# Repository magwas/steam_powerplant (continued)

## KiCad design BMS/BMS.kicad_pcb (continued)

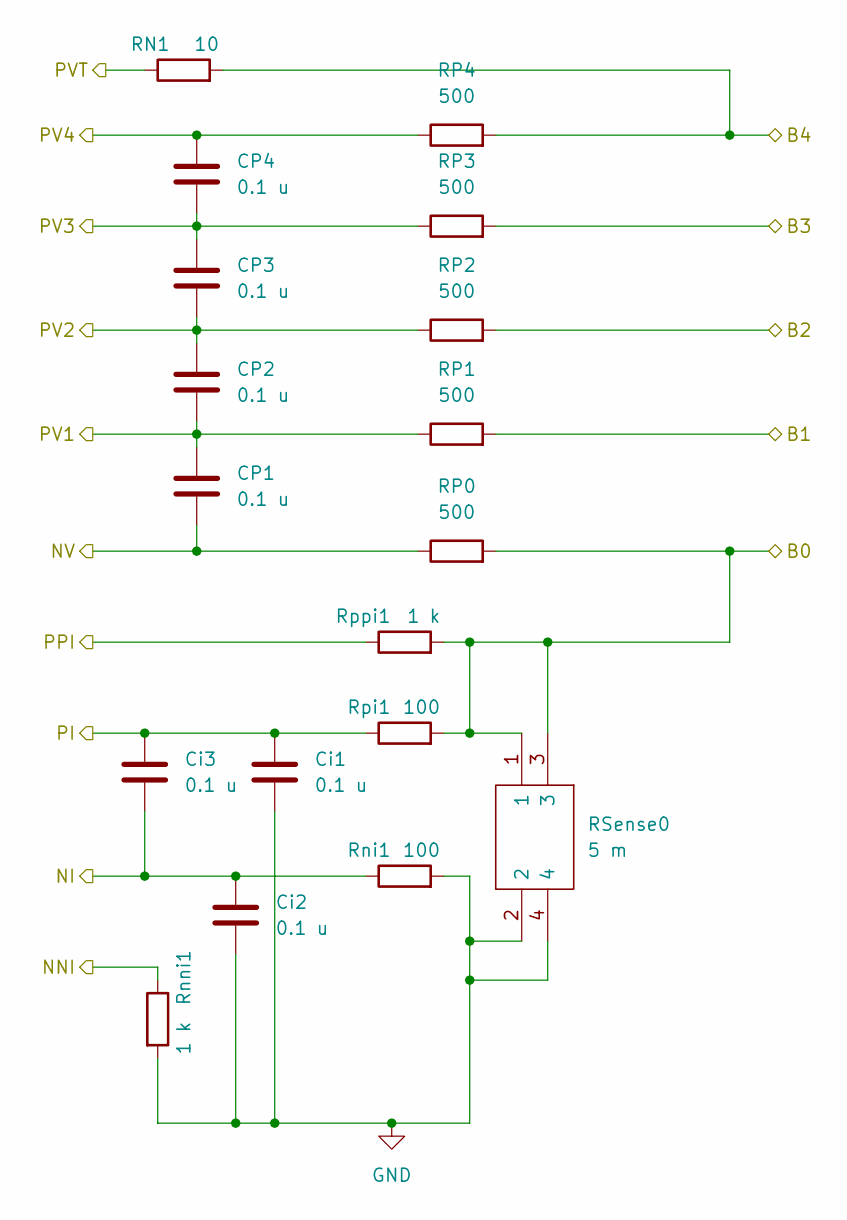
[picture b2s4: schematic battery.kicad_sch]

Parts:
CP1, CP2, CP3, CP4: 0.1 u; C_0603_1608Metric; Manufacturer_Part_Number KAM15AR71H104KT
Ci1, Ci2, Ci3: 0.1 u; C_0603_1608Metric; Manufacturer_Part_Number KAM15AR71H104KT
RN1: 10; R_0402_1005Metric; Manufacturer_Part_Number ERJ-U0XF10R0Y
RP0, RP1, RP2, RP3, RP4: 500; R_1206_3216Metric; Manufacturer_Part_Number MCA12060D5000BP500
RSense0: 5 m; Y14880R00500B9R; Mouser Part Number 71-CSM36370R0050BST
Rni1: 100; R_0603_1608Metric; Manufacturer_Part_Number APC0603T100RZ
Rnni1: 1 k; R_0402_1005Metric; Manufacturer_Part_Number 71-PTN0402Y5000BST1
Rpi1: 100; R_0603_1608Metric; Manufacturer_Part_Number APC0603T100RZ
Rppi1: 1 k; R_0402_1005Metric; Manufacturer_Part_Number 71-PTN0402Y5000BST1

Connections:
/Battery/B0: RP0.2, RSense0.1, RSense0.3, Rpi1.2, Rppi1.2; also elsewhere on the board
/Battery/B1: RP1.2; also elsewhere on the board
/Battery/B2: RP2.2; also elsewhere on the board
/Battery/B3: RP3.2; also elsewhere on the board
/Battery/B4: RN1.2, RP4.2; also elsewhere on the board
/Battery/NI: Ci2.2, Ci3.1, Rni1.1; also elsewhere on the board
/Battery/NNI: Rnni1.1; also elsewhere on the board
/Battery/NV: CP1.1, RP0.1; also elsewhere on the board
/Battery/PI: Ci1.2, Ci3.2, Rpi1.1; also elsewhere on the board
/Battery/PPI: Rppi1.1; also elsewhere on the board
/Battery/PV1: CP1.2, CP2.1, RP1.1; also elsewhere on the board
/Battery/PV2: CP2.2, CP3.1, RP2.1; also elsewhere on the board
/Battery/PV3: CP3.2, CP4.1, RP3.1; also elsewhere on the board
/Battery/PV4: CP4.2, RP4.1; also elsewhere on the board
/Battery/PVT: RN1.1; also elsewhere on the board
GND: Ci1.1, Ci2.1, RSense0.2, RSense0.4, Rni1.2, Rnni1.2; also elsewhere on the board

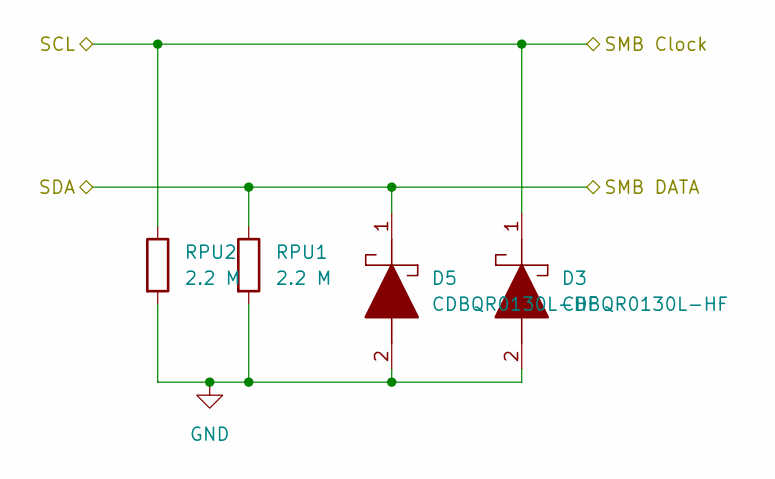
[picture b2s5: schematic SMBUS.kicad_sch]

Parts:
D3, D5: CDBQR0130L-HF; D_0402_1005Metric; Manufacturer_Part_Number CDBQR0130L-HF
RPU1, RPU2: 2.2 M; R_2010_5025Metric; Manufacturer_Part_Number RCV20102M20JNEF

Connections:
/SMBUS/SCL: D3.1, RPU2.1; also elsewhere on the board
/SMBUS/SDA: D5.1, RPU1.1; also elsewhere on the board
GND: D3.2, D5.2, RPU1.2, RPU2.2; also elsewhere on the board

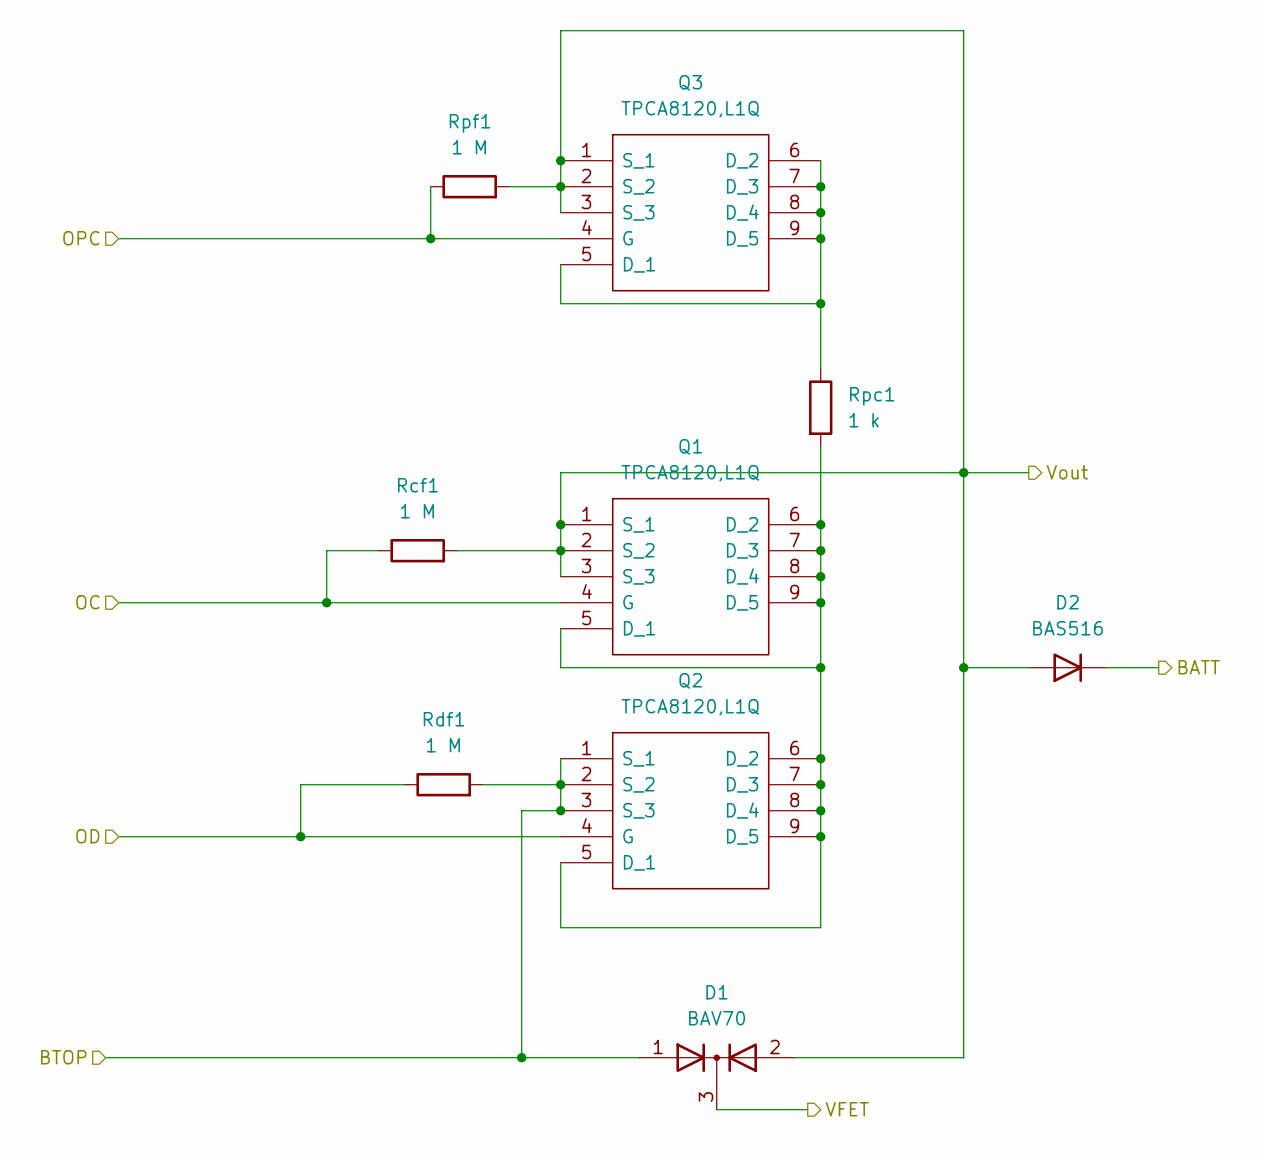
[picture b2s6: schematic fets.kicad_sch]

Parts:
D1: BAV70; SOT-23; Manufacturer_Part_Number BAV70,215
D2: BAS516; D_SOD-523; Manufacturer_Part_Number BAS516,135
Q1, Q2, Q3: TPCA8120,L1Q; TPH4R003NLL1Q; Mouser Part Number 757-TPCA8120L1Q
Rcf1: 1 M; R_0402_1005Metric; Manufacturer_Part_Number 560112110033
Rdf1: 1 M; R_0402_1005Metric; Manufacturer_Part_Number 560112110033
Rpc1: 1 k; R_2512_6332Metric; Manufacturer_Part_Number 71-PTN0402Y5000BST1
Rpf1: 1 M; R_0402_1005Metric; Manufacturer_Part_Number 560112110033

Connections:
/Battery/B4: D1.1 (A), Q2.1 (S_1), Q2.2 (S_2), Q2.3 (S_3), Rdf1.2; also elsewhere on the board
/FETs/BATT: D2.1 (K); also elsewhere on the board
/FETs/OC: Q1.4 (G), Rcf1.1; also elsewhere on the board
/FETs/OD: Q2.4 (G), Rdf1.1; also elsewhere on the board
/FETs/OPC: Q3.4 (G), Rpf1.1; also elsewhere on the board
/FETs/VFET: D1.3 (K); also elsewhere on the board
/FETs/Vout: D1.2 (A), D2.2 (A), Q1.1 (S_1), Q1.2 (S_2), Q1.3 (S_3), Q3.1 (S_1), Q3.2 (S_2), Q3.3 (S_3), Rcf1.2, Rpf1.2; also elsewhere on the board
unnamed: Q1.5 (D_1), Q1.6 (D_2), Q1.7 (D_3), Q1.8 (D_4), Q1.9 (D_5), Q2.5 (D_1), Q2.6 (D_2), Q2.7 (D_3), Q2.8 (D_4), Q2.9 (D_5), Rpc1.2
unnamed: Q3.5 (D_1), Q3.6 (D_2), Q3.7 (D_3), Q3.8 (D_4), Q3.9 (D_5), Rpc1.1

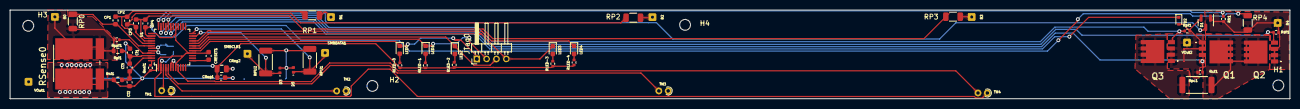
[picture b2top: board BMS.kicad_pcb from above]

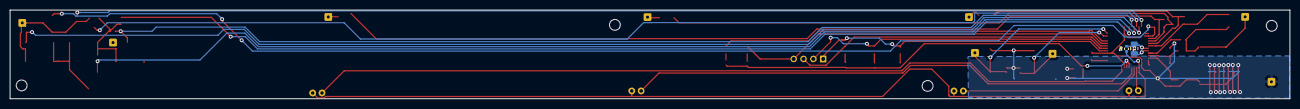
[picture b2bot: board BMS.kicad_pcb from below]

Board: 2 copper layers, 260.0 x 18.0 mm, 65 parts (2 on the bottom side), 45 nets.

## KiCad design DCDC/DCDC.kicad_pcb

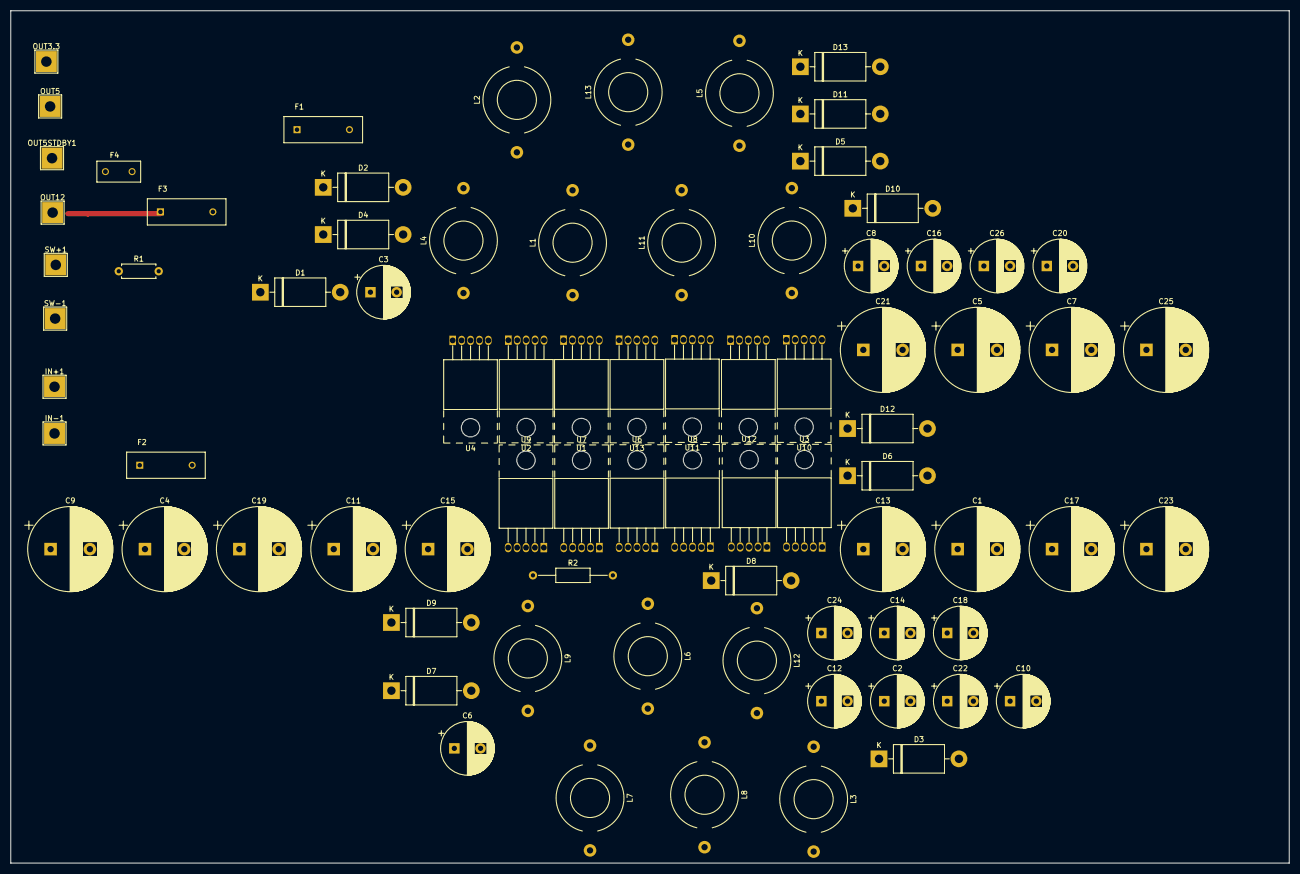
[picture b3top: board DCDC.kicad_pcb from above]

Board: 2 copper layers, 243.8 x 162.6 mm, 79 parts (0 on the bottom side), 24 nets.

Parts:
C1, C4, C5, C7, C9, C11, C13, C15, C17, C19, C21, C23, C25: 100 uF; CP_Radial_D16.0mm_P7.50mm
C2, C3, C6, C8, C10, C12, C14, C16, C18, C20, C22, C24, C26: 1000 uF; CP_Radial_D10.0mm_P5.00mm
D1, D2, D3, D4, D5, D6, D7, D8, D9, D10, D11, D12, D13: 1N5822; D_DO-201AD_P15.24mm_Horizontal
F1, F2, F3: 30R600; CAPRB1000W55L1500T500H1900
F4: 30R160; FUSRR508W60L835T400H810
IN+1: Conn_01x01; TestPoint_THTPad_4.0x4.0mm_Drill2.0mm
IN-1: Conn_01x01; TestPoint_THTPad_4.0x4.0mm_Drill2.0mm
L1, L2, L3, L4, L5, L6, L7, L8, L9, L10, L11, L12, L13: 100 uH; L_Toroid_Horizontal_D12.7mm_P20.00mm_Diameter14-5mm_Amidon-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
OUT3.3, OUT5, OUT5STDBY1, OUT12: Conn_01x01; TestPoint_THTPad_4.0x4.0mm_Drill2.0mm
R1: 10 kOhm; R_Axial_DIN0207_L6.3mm_D2.5mm_P7.62mm_Horizontal
R2: 100 kOhm; R_Axial_DIN0207_L6.3mm_D2.5mm_P15.24mm_Horizontal
SW+1: Conn_01x01; TestPoint_THTPad_4.0x4.0mm_Drill2.0mm
SW-1: Conn_01x01; TestPoint_THTPad_4.0x4.0mm_Drill2.0mm
U1, U5, U6, U11: LM2576T-3.3; TO-220-5_Horizontal_TabUp
U2, U3, U7, U9, U12: LM2576T-5; TO-220-5_Horizontal_TabUp
U4, U8, U10, U13: LM2576T-12; TO-220-5_Horizontal_TabUp

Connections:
GND: C1.2, C2.2, C3.2, C4.2, C5.2, C6.2, C7.2, C8.2, C9.2, C10.2, C11.2, C12.2, C13.2, C14.2, C15.2, C16.2, C17.2, C18.2, C19.2, C20.2, C21.2, C22.2, C23.2, C24.2, C25.2, C26.2, D1.2 (A), D2.2 (A), D3.2 (A), D4.2 (A), D5.2 (A), D6.2 (A), D7.2 (A), D8.2 (A), D9.2 (A), D10.2 (A), D11.2 (A), D12.2 (A), D13.2 (A), IN-1.1, R2.1, U1.3 (GND), U2.3 (GND), U2.5 (~ON/OFF), U3.3 (GND), U4.3 (GND), U5.3 (GND), U6.3 (GND), U7.3 (GND), U8.3 (GND), U9.3 (GND), U10.3 (GND), U11.3 (GND), U12.3 (GND), U13.3 (GND)
unnamed: D1.1 (K), L1.1, U1.2 (OUT)
unnamed: D2.1 (K), L2.1, U2.2 (OUT)
unnamed: D3.1 (K), L3.1, U3.2 (OUT)
unnamed: D4.1 (K), L4.1, U4.2 (OUT)
unnamed: D5.1 (K), L5.1, U5.2 (OUT)
unnamed: D6.1 (K), L6.1, U6.2 (OUT)
unnamed: D7.1 (K), L7.1, U7.2 (OUT)
unnamed: D8.1 (K), L8.1, U8.2 (OUT)
unnamed: D9.1 (K), L9.1, U9.2 (OUT)
unnamed: D10.1 (K), L10.1, U10.2 (OUT)
unnamed: D11.1 (K), L11.1, U11.2 (OUT)
unnamed: D12.1 (K), L12.1, U12.2 (OUT)
unnamed: D13.1 (K), L13.1, U13.2 (OUT)
unnamed: F1.1, OUT3.3.1
unnamed: F2.1, OUT5.1
unnamed: F4.1, OUT5STDBY1.1
unnamed: R1.1, SW+1.1
ON/OFF: R2.2, SW-1.1, U1.5 (~ON/OFF), U3.5 (~ON/OFF), U4.5 (~ON/OFF), U5.5 (~ON/OFF), U6.5 (~ON/OFF), U7.5 (~ON/OFF), U8.5 (~ON/OFF), U9.5 (~ON/OFF), U10.5 (~ON/OFF), U11.5 (~ON/OFF), U12.5 (~ON/OFF), U13.5 (~ON/OFF)
V3.3: C2.1, C10.1, C12.1, C22.1, F1.2, L1.2, L5.2, L6.2, L11.2, U1.4 (FB), U5.4 (FB), U6.4 (FB), U11.4 (FB)
V5: C6.1, C14.1, C18.1, C24.1, F2.2, L3.2, L7.2, L9.2, L12.2, U3.4 (FB), U7.4 (FB), U9.4 (FB), U12.4 (FB)
V5 STDBY: C3.1, F4.2, L2.2, R1.2, U2.4 (FB)
V12: C8.1, C16.1, C20.1, C26.1, F3.2, L4.2, L8.2, L10.2, L13.2, U4.4 (FB), U8.4 (FB), U10.4 (FB), U13.4 (FB)
Vin: C1.1, C4.1, C5.1, C7.1, C9.1, C11.1, C13.1, C15.1, C17.1, C19.1, C21.1, C23.1, C25.1, IN+1.1, U1.1 (VIN), U2.1 (VIN), U3.1 (VIN), U4.1 (VIN), U5.1 (VIN), U6.1 (VIN), U7.1 (VIN), U8.1 (VIN), U9.1 (VIN), U10.1 (VIN), U11.1 (VIN), U12.1 (VIN), U13.1 (VIN)

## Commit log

2024-01-28 initial checkin
2024-01-28 README
2024-01-28 top is filleted, gathering cnc jobs
2024-01-28 added picoPSU to the part list
2024-01-29 new dc/dc converter design
2024-01-29 BOM for DC/DC converter
2024-02-01 redesign of voltage regulator
2024-02-02 restructured schematics, dumbed down pcb before redesign
2024-02-02 pcb part for 5V ready
2024-02-02 pcb updated with all parts
2024-02-02 BOMs
2024-02-02 pcb designed for 3 outputs
2024-02-07 dcdc simulation, mechanical drawings
2024-02-07 all cutholes are rounded
2024-02-07 one module of the dcdc converter seems ready again...
2024-02-10 3 modules of DCDC, hinge
2024-02-12 handle
2024-02-28 BMS from Atmel datasheet. trying to figure out CNC of the pump and handle
2024-03-05 DCDC fix unavailable parts, BMS redesign, handle fix, rearrange top half
2024-03-13 bottom redesign
2024-03-15 keyboard
2024-03-16 bottom rearrange
2024-03-16 cooling topper and viewport
2024-03-18 coil redesign, materials
